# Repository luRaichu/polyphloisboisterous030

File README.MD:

# Polyphloisboisterous '030

This is my 16 MHz 68030 microprocessor upgrade board for Apple's Macintosh Plus, derived from the [reverse-engineered](https://github.com/alxlab-zone66x/Performer-SE-PL-CL/tree/main) MicroMac Performer. It is designed for easy and low-cost assembly by hobbyists.

I created it because I didn't want to pay the relatively high manufacturing costs to get five Performer clone boards made, and I would have a hard time surface mount soldering the GALs.

My board is 50% smaller and 77% cheaper to manufacture over the original Performer, and doesn't use any dense SMD footprints. It can be assembled by anyone who can recap a vintage computer motherboard.

The provided PCB files are licensed under CC BY-NC-SA - they're NOT intended for commercial use.

## Notes on GALs

The original Performer GALs have been dumped. GAL16V8-15, PALCE16V8-15, and ATF16V8-15 have been tested as suitable replacements.

I used ATF16V8B-15JU, they are in stock at DigiKey and Mouser.

Faster/slower chips haven't been tested so far.

I used [afterburner](https://github.com/ole00/afterburner) to program GALs cheaply.

## Why is the FPU missing?

Because it's seldomly used on the Macintosh, and the PCB layout is simpler without it. There's not much point in having super fast floating point math when very little software uses it and if it'll be bottlenecked by the 16 MHz CPU and 16-bit data bus.

## Bill of Materials

|Quantity|Description|Designators|
|--------|-----------|-----------|
|16|4.7 kΩ resistor, 1/4W or better, 1206 package|R1, R2, R3, R4, R5, R6, R7, R8, R9, R10, R11, R12, R13, R14, R15, R16|
|6|0.1μF ceramic capacitor, 6.3V or better, 1206 package|C4, C5, C6, C7, C8, C9|
|2|22μF tantalum capacitor, 10V or better, 2312 package|C1, C3|
|5|20 (4 x 5) pos. PLCC socket, through hole|U3, U4, U5, U6, U7|
|5|16V8 GALs or PALs, ATF16V8 recommended|U3, U4, U5, U6, U7|
|1|**Optional:** PGA-128 socket or equivalent for 68030. I used discrete machined pin headers|U1|
|1|MC68030, PGA, at least 16 MHz|U1|
||Headers and sockets to stack Polyphloisboisterous '030 on top of 68000. I used two 32 pos. round pin headers with a 64 (2 x 32) pos. machined pin DIP socket|IC1|

## Revision History
* 11/27/2025 Rev. 0 - First version
* 12/26/2025 Rev. 1 - Made board slightly shorter to help clear top of SIMM 1

## Assembly
1. Solder passives (resistors, capacitors) to board.

2. Solder GAL sockets to board.

3. Either solder PGA socket to board or permanently solder 68030 directly to board. In my case, I pushed individual pin headers onto the 68030 before soldering it. See [this graphic](img/cpuheaders-diagram.png) for my placement of these headers.

4. Solder 68000 piggyback connector(s) (i.e. male pin headers) to board.

5. Program GALs and insert into sockets.

Your board should look like this:

## Installation
1. Solder piggyback connector (i.e. female machined pin DIP socket) on top of the 68000 microprocessor on the Macintosh Plus logic board.

2. Seat the Polyphloisboisterous '030 accelerator on top of the 68000. It should look as pictured. Be mindful of the top of SIMM 1.

3. Make a test: Have the logic board next to the Mac and connect the multicolored wire harness. Make sure that the logic board or accelerator do not touch any metal part of the chassis. Turn power on and listen for the beep. If you get a beep the accelerator is working. Turn power off and continue with the installation.

4. Carefully slide the logic board back into position while watching the accelerator **or** alternatively slide it **underneath** the rails and into the chassis, then slot the logic board into a rail on one side and bend the chassis on the other side in such a way that the logic board does go into the other rail as well.

5. Download the correct version of the [GemStart Universal](https://macintoshgarden.org/apps/accelerator-card-drivers) driver for your System Software. You will need:

    * GemStart 2.2 for System 6
    * GemStart 3.0 for System 7.0 (not recommended)
    * GemStart 7.1 for System 7.1

    If asked, identify your accelerator as a "Total Systems Mercury" in the installer (it is logically identical to this one). GemStart should show that you have a 16 MHz 68030.

## Performance

I tested System 6.0.8 and 7.1 with this accelerator, both booted from my external BlueSCSI disk emulator.

Here are the benchmark results from Speedometer 3.23:

To temporarily disable the Polyphloisboisterous '030 (and similar upgrades) using the Programmer's Switch, hold Interrupt after the boot chime then quickly press Reset. After the second chime release Interrupt. The upgrade is disabled until the next boot.

It appears that these accelerators affect the Macintosh's Sound Manager. Audio playback may be garbled or cut in and out rapidly. I don't know why.

## Thanks
To Bolle and Trash80toHP_Mini of 68kMLA forums, for reverse engineering the Mercury 030 and MicroMac Performer.

To alxlab-zone66x, for converting the Performer EAGLE files to a KiCad project.

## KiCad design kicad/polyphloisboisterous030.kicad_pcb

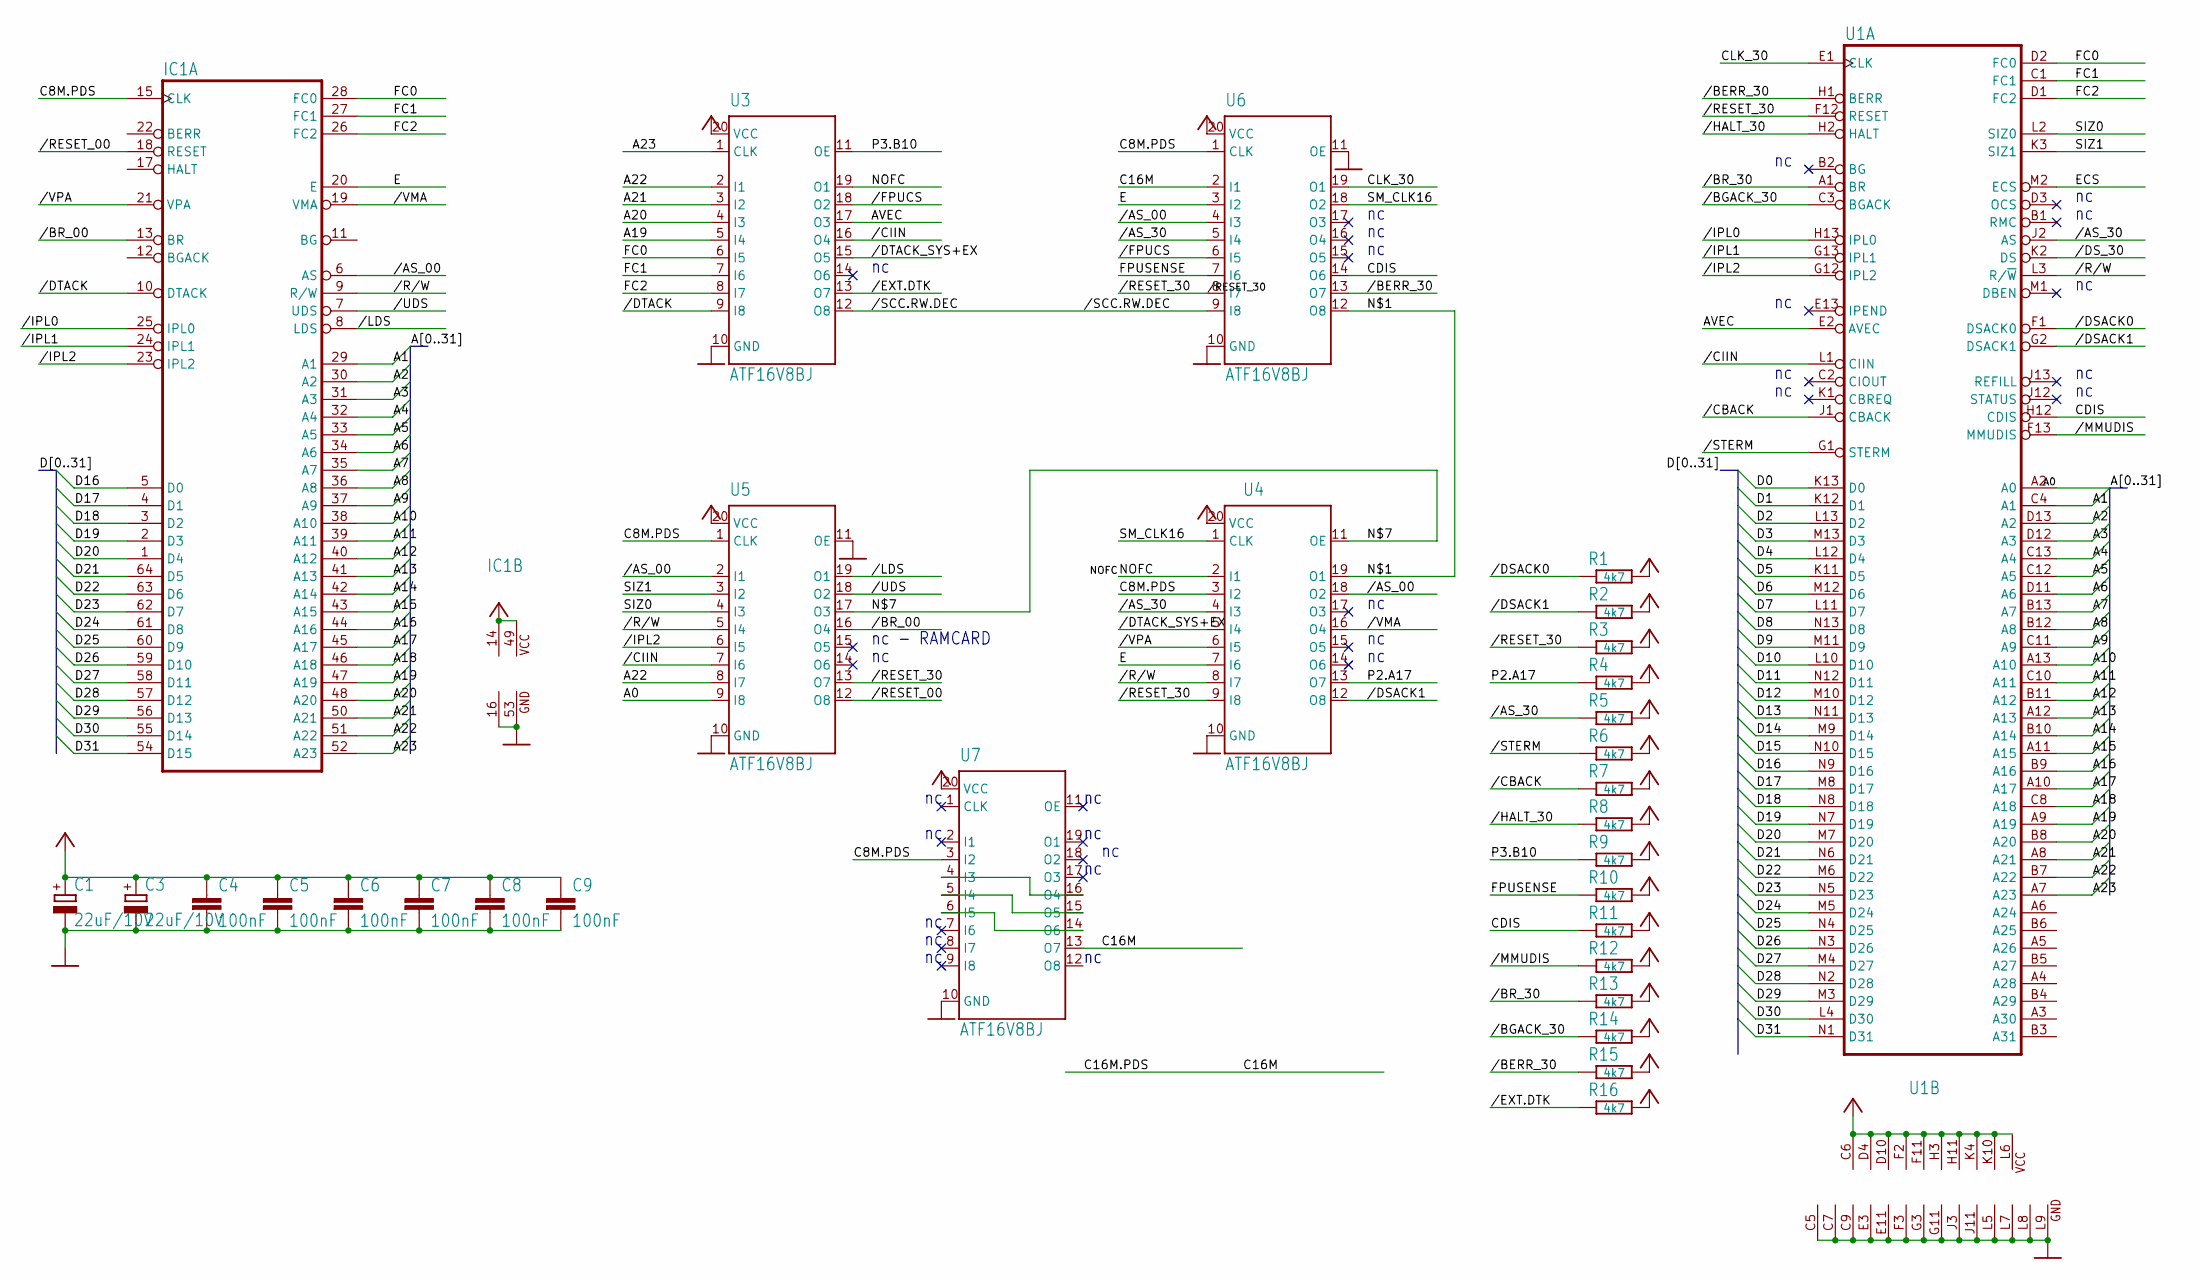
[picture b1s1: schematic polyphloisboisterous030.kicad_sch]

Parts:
C1, C3: 22uF/10V; CP_EIA-6032-15_Kemet-U_Pad2.25x2.35mm_HandSolder
C4, C5, C6, C7, C8, C9: 100nF; C_1206_3216Metric_Pad1.60x1.80mm_HandSolder
IC1: MC68000P; DIP-64_W22.86mm_LongPads_Mirror
R1, R2, R3, R4, R5, R6, R7, R8, R9, R10, R11, R12, R13, R14, R15, R16: 4k7; R_1206_3216Metric_Pad1.60x1.80mm_HandSolder
U1: MC68030RC; CPGA-128_Layout13x13_MC68030
U3, U4, U5, U6, U7: ATF16V8BJ; PLCC-20_THT-Socket

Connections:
/A0: U1.A2 (A0), U5.9 (I8)
/A1: IC1.29 (A1), U1.C4 (A1)
/A2: IC1.30 (A2), U1.D13 (A2)
/A3: IC1.31 (A3), U1.D12 (A3)
/A4: IC1.32 (A4), U1.C13 (A4)
/A5: IC1.33 (A5), U1.C12 (A5)
/A6: IC1.34 (A6), U1.D11 (A6)
/A7: IC1.35 (A7), U1.B13 (A7)
/A8: IC1.36 (A8), U1.B12 (A8)
/A9: IC1.37 (A9), U1.C11 (A9)
/A10: IC1.38 (A10), U1.A13 (A10)
/A11: IC1.39 (A11), U1.C10 (A11)
/A12: IC1.40 (A12), U1.B11 (A12)
/A13: IC1.41 (A13), U1.A12 (A13)
/A14: IC1.42 (A14), U1.B10 (A14)
/A15: IC1.43 (A15), U1.A11 (A15)
/A16: IC1.44 (A16), U1.B9 (A16)
/A17: IC1.45 (A17), U1.A10 (A17)
/A18: IC1.46 (A18), U1.C8 (A18)
/A19: IC1.47 (A19), U1.A9 (A19), U3.5 (I4)
/A20: IC1.48 (A20), U1.B8 (A20), U3.4 (I3)
/A21: IC1.50 (A21), U1.A8 (A21), U3.3 (I2)
/A22: IC1.51 (A22), U1.B7 (A22), U3.2 (I1), U5.8 (I7)
/A23: IC1.52 (A23), U1.A7 (A23), U3.1 (CLK)
/AVEC: U1.E2 (AVEC), U3.17 (O3)
/C8M.PDS: IC1.15 (CLK), U4.3 (I2), U5.1 (CLK), U6.1 (CLK), U7.3 (I2)
/C16M: U6.2 (I1), U7.13 (O7)
/CDIS: R11.1, U1.H12 (CDIS), U6.14 (O6)
/CLK_30: U1.E1 (CLK), U6.19 (O1)
/D0: U1.K13 (D0)
/D1: U1.K12 (D1)
/D2: U1.L13 (D2)
/D3: U1.M13 (D3)
/D4: U1.L12 (D4)
/D5: U1.K11 (D5)
/D6: U1.M12 (D6)
/D7: U1.L11 (D7)
/D8: U1.N13 (D8)
/D9: U1.M11 (D9)
/D10: U1.L10 (D10)
/D11: U1.N12 (D11)
/D12: U1.M10 (D12)
/D13: U1.N11 (D13)
/D14: U1.M9 (D14)
/D15: U1.N10 (D15)
/D16: IC1.5 (D0), U1.N9 (D16)
/D17: IC1.4 (D1), U1.M8 (D17)
/D18: IC1.3 (D2), U1.N8 (D18)
/D19: IC1.2 (D3), U1.N7 (D19)
/D20: IC1.1 (D4), U1.M7 (D20)
/D21: IC1.64 (D5), U1.N6 (D21)
/D22: IC1.63 (D6), U1.M6 (D22)
/D23: IC1.62 (D7), U1.N5 (D23)
/D24: IC1.61 (D8), U1.M5 (D24)
/D25: IC1.60 (D9), U1.N4 (D25)
/D26: IC1.59 (D10), U1.N3 (D26)
/D27: IC1.58 (D11), U1.M4 (D27)
/D28: IC1.57 (D12), U1.N2 (D28)
/D29: IC1.56 (D13), U1.M3 (D29)
/D30: IC1.55 (D14), U1.L4 (D30)
/D31: IC1.54 (D15), U1.N1 (D31)
/E: IC1.20 (E), U4.7 (I6), U6.3 (I2)
/ECS: U1.M2 (ECS)
/FC0: IC1.28 (FC0), U1.D2 (FC0), U3.6 (I5)
/FC1: IC1.27 (FC1), U1.C1 (FC1), U3.7 (I6)
/FC2: IC1.26 (FC2), U1.D1 (FC2), U3.8 (I7)
/FPUSENSE: R10.1, U6.7 (I6)
/N$1: U4.19 (O1), U6.12 (O8)
/N$7: U4.11 (OE), U5.17 (O3)
/NOFC: U3.19 (O1), U4.2 (I1)
/P2.A17: R4.1, U4.13 (O7)
/P3.B10: R9.1, U3.11 (OE)
/SIZ0: U1.L2 (SIZ0), U5.4 (I3)
/SIZ1: U1.K3 (SIZ1), U5.3 (I2)
/SM_CLK16: U4.1 (CLK), U6.18 (O2)
//AS_00: IC1.6 (AS), U4.18 (O2), U5.2 (I1), U6.4 (I3)
//AS_30: R5.1, U1.J2 (AS), U4.4 (I3), U6.5 (I4)
//BERR_30: R15.1, U1.H1 (BERR), U6.13 (O7)
//BGACK_30: R14.1, U1.C3 (BGACK)
//BR_00: IC1.13 (BR), U5.16 (O4)
//BR_30: R13.1, U1.A1 (BR)
//CBACK: R7.1, U1.J1 (CBACK)
//CIIN: U1.L1 (CIIN), U3.16 (O4), U5.7 (I6)
//DSACK0: R1.1, U1.F1 (DSACK0)
//DSACK1: R2.1, U1.G2 (DSACK1), U4.12 (O8)
//DS_30: U1.K2 (DS)
//DTACK: IC1.10 (DTACK), U3.9 (I8)
//DTACK_SYS+EX: U3.15 (O5), U4.5 (I4)
//EXT.DTK: R16.1, U3.13 (O7)
//FPUCS: U3.18 (O2), U6.6 (I5)
//HALT_30: R8.1, U1.H2 (HALT)
//IPL0: IC1.25 (IPL0), U1.H13 (IPL0)
//IPL1: IC1.24 (IPL1), U1.G13 (IPL1)
//IPL2: IC1.23 (IPL2), U1.G12 (IPL2), U5.6 (I5)
//LDS: IC1.8 (LDS), U5.19 (O1)
//MMUDIS: R12.1, U1.F13 (MMUDIS)
//RESET_00: IC1.18 (RESET), U5.12 (O8)
//RESET_30: R3.1, U1.F12 (RESET), U4.9 (I8), U5.13 (O7), U6.8 (I7)
//R/W: IC1.9 (R/W), U1.L3 (R/~W), U4.8 (I7), U5.5 (I4)
//SCC.RW.DEC: U3.12 (O8), U6.9 (I8)
//STERM: R6.1, U1.G1 (STERM)
//UDS: IC1.7 (UDS), U5.18 (O2)
//VMA: IC1.19 (VMA), U4.16 (O4)
//VPA: IC1.21 (VPA), U4.6 (I5)
GND: C1.-, C3.-, C4.2, C5.2, C6.2, C7.2, C8.2, C9.2, IC1.16 (GND@1), IC1.53 (GND@2), U1.C5 (GND@1), U1.C7 (GND@2), U1.C9 (GND@3), U1.E3 (GND@4), U1.E11 (GND@5), U1.F3 (GND@6), U1.G3 (GND@7), U1.G11 (GND@8), U1.J3 (GND@9), U1.J11 (GND@10), U1.L5 (GND@11), U1.L7 (GND@12), U1.L8 (GND@13), U1.L9 (GND@14), U3.10 (GND), U4.10 (GND), U5.10 (GND), U5.11 (OE), U6.10 (GND), U6.11 (OE), U7.10 (GND)
unnamed: U7.4 (I3), U7.16 (O4)
unnamed: U7.5 (I4), U7.15 (O5)
unnamed: U7.6 (I5), U7.14 (O6)
VCC: C1.+, C3.+, C4.1, C5.1, C6.1, C7.1, C8.1, C9.1, IC1.14 (VCC@1), IC1.49 (VCC@2), R1.2, R2.2, R3.2, R4.2, R5.2, R6.2, R7.2, R8.2, R9.2, R10.2, R11.2, R12.2, R13.2, R14.2, R15.2, R16.2, U1.C6 (VCC@1), U1.D4 (VCC@2), U1.D10 (VCC@3), U1.F2 (VCC@4), U1.F11 (VCC@5), U1.H3 (VCC@6), U1.H11 (VCC@7), U1.K4 (VCC@8), U1.K10 (VCC@9), U1.L6 (VCC@10), U3.20 (VCC), U4.20 (VCC), U5.20 (VCC), U6.20 (VCC), U7.20 (VCC)

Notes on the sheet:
nc - RAMCARD

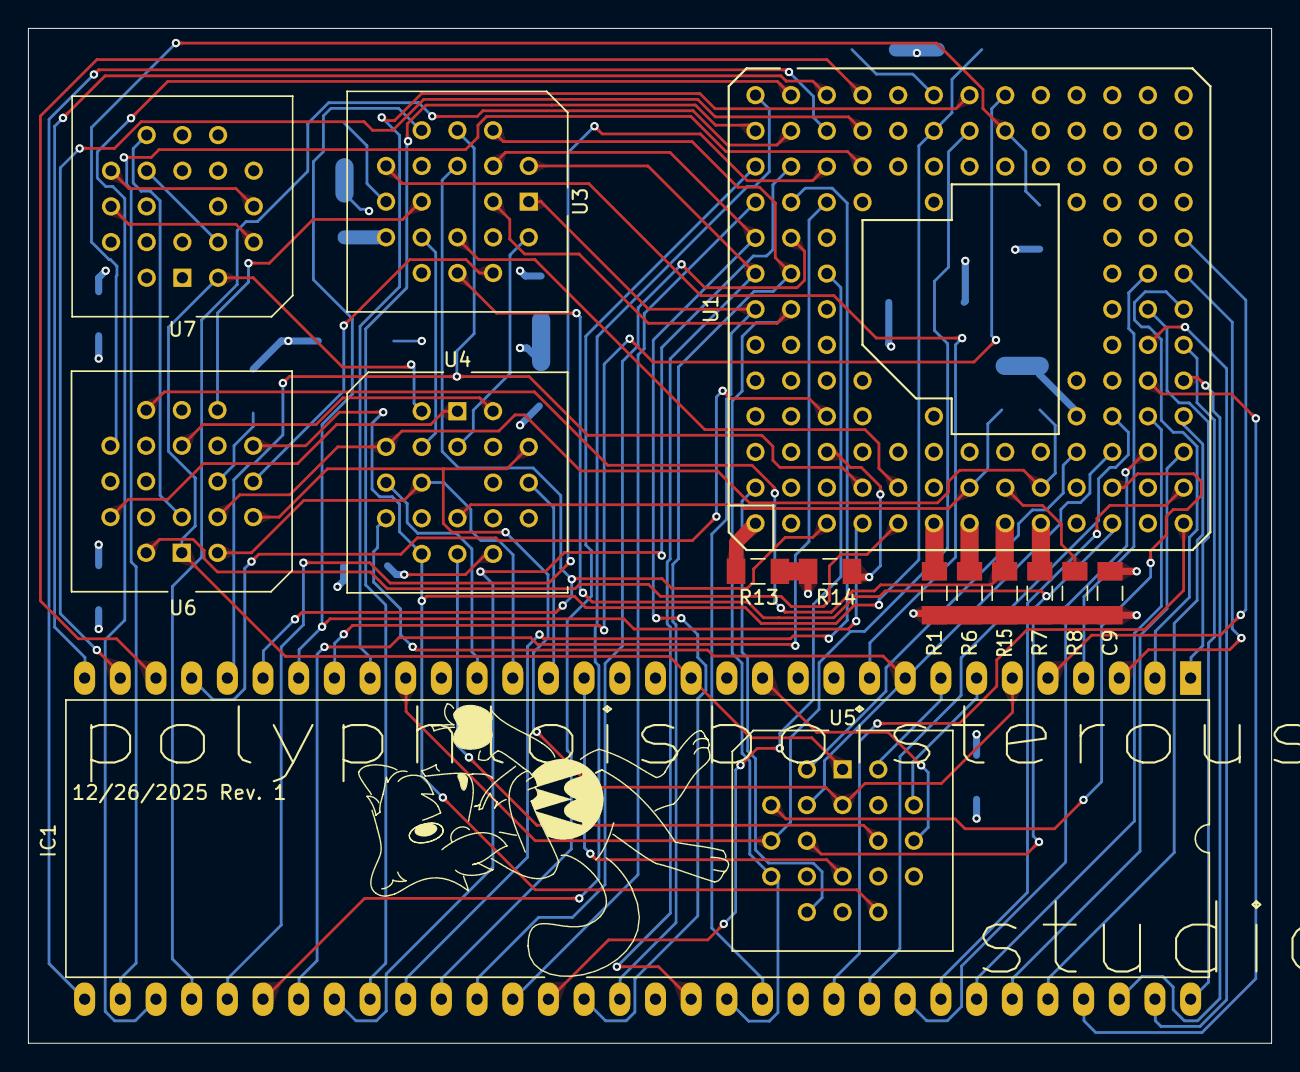
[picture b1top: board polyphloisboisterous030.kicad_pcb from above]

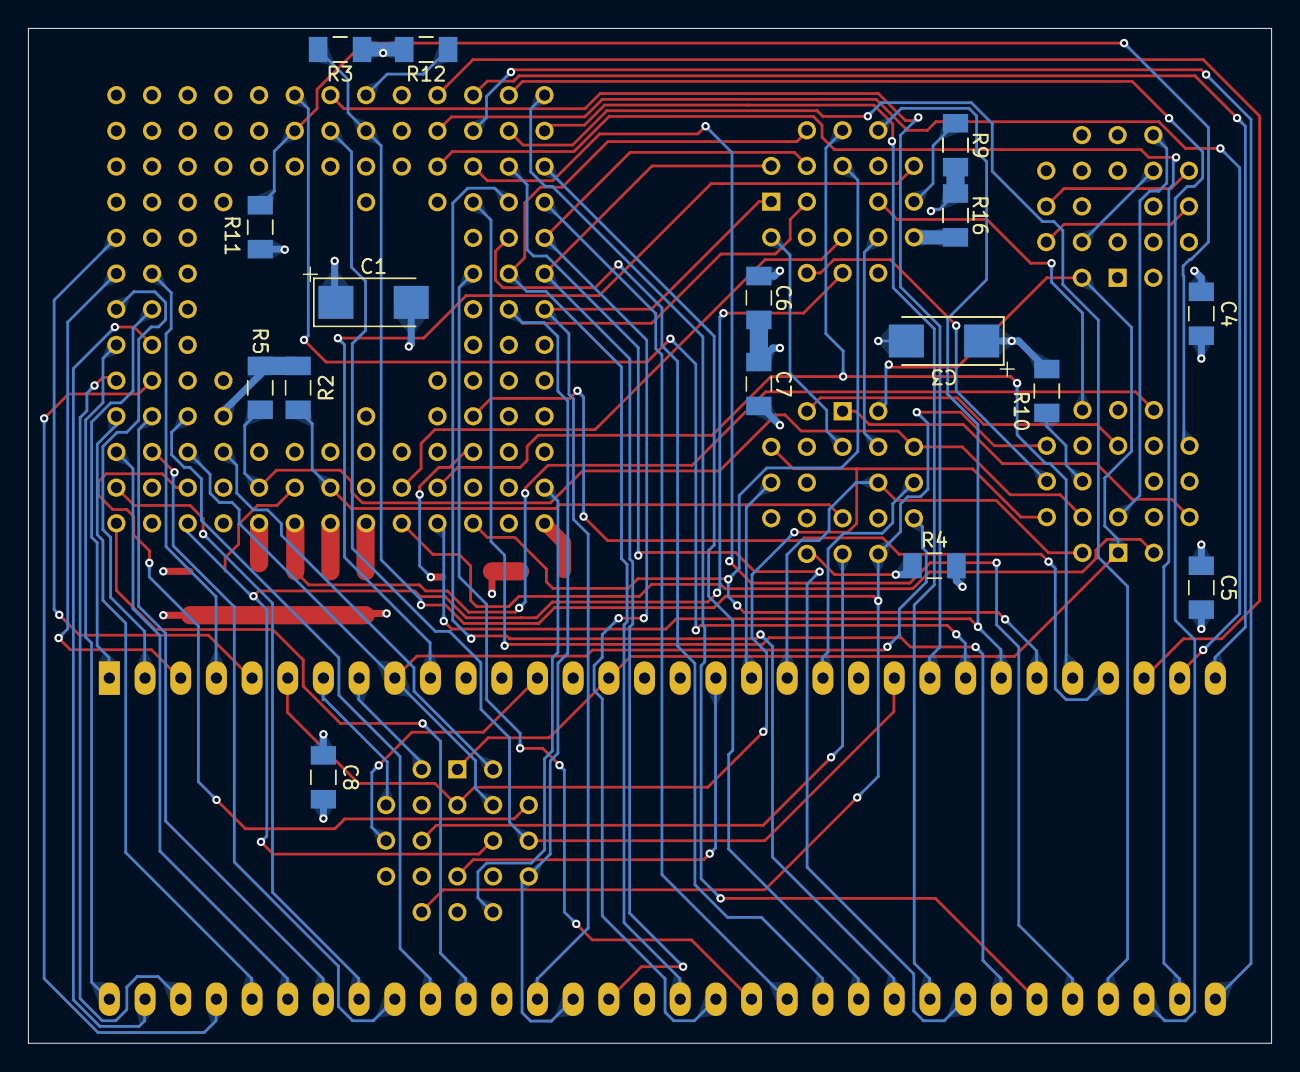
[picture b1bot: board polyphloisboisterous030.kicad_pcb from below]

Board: 4 copper layers, 88.5 x 72.2 mm, 31 parts (16 on the bottom side), 91 nets.

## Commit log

2025-12-27 add Polyphloisboisterous '030 files
2025-12-27 correct photo on README
2026-01-02 update README & add schematics pdf
2026-01-10 recommend GemStart and add note on sound playback
